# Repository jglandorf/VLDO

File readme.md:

## A Very Low Dropout Regulator Based on G4COL / ND6T

Implemented for use with the [QMX+ HF transceiver](https://qrp-labs.com/qmxp.html).  
PCB designed in KiCAD v9.

References:  
https://www.gqrp.com/limiter.jpg (
via https://groups.io/g/QRPLabs/topic/qmx_battery/111670594)  
http://www.nd6t.com/qrp/VLDO.htm

PCB, top  

PCB, bottom  

Schematic  

PCB layout  

LTSpice schematic for static simulation  

### Output Voltage with a 5V LDO 
The schematic uses a 5V LDO as the reference voltage.  The output voltage is given by: 
```  
Vldo = Vout * (R4 / (R3 + R4))
Vout = Vldo / (R4 / (R3 + R4))
12.5V = 5V / ( 20k / (30k + 20k))
11.8V = 5V / ( 22k / (30k + 22k))
8.85V = 5V / (39k / (30k + 39k))
```  
In practice, depending on the quality of transistors used, you may need to tweak the value of R3 or R4.

### Parts Tested in Prototype  
The PCB has alternate footprints for the active components so that alternative parts may be tested, or that the PCB may be built mostly surface-mount or through-hole.  

| RefDes | Part | Source | Comments           |   
| ------ | ----------- | -------------------- | ------------------------------------ |  
| M1 | IRF4905S | https://www.aliexpress.us/item/3256806571411100.html | (TO-263) Works, but runs hotter than expected; Rds_on likely much higher than spec
| M1 | IRF4905 | https://www.aliexpress.us/item/3256806880410046.html | (TO-220 alternate) Part from this supplier does not work well  
| U3 | ME6203A50M3G  | https://www.aliexpress.us/item/3256806655687105.html | (SOT23-3) Works well  
| Q3/Q4 | MMBT2222A  | https://www.aliexpress.us/item/3256806768261444.html | (SOT23-3) Works well  

### Power In/Out Connectors  
The prototype used Anderson PowerPole [PP15/30/45 housings](https://powerwerx.com/anderson-powerpole-colored-housings) with [PP45 crimp pins](https://powerwerx.com/anderson-261g2-powerpole-contact-pp45) as these were on hand -- not the [special PCB-mount pins](https://powerwerx.com/printed-circuit-board-pcb-contact-25amp).  
The PCB is designed for 14 AWG solid wire. To fit 14 AWG solid wire into a PP45 pin (which is designed for 10 AWG wire), it is folded over at the pin end, then soldered into the PP45 pin.  PP30 pins are deisgned for 12-14 AWG wire and should solder in directly.

14 AWG Wire folded over for PowerPole crimp pin  

14 AWG Wire soldered into PowerPole crimp pin  

14 AWG Wire soldered into PCB (be sure to cut excess lead length off)  

### Thermal Test  
Although the [QMX+](https://qrp-labs.com/qmxp.html) is specified to consume slightly less than 1 amp at 12 volts, the VLDO prototype was tested with a [WEL-3005 30W constant-current load tester](https://www.hackster.io/john-bradnam/30w-constant-current-load-65ecdd) at 2.5A.  
When using parts from AliExpress or of unknown pedigree, it is recommended that VLDO operating conditions do not exceed those normally expected for the QMX+; i.e., 1A@2 minutes (TX) / 0.1A@2 minutes (RX).   

Vin=13.24, Vout=12V (nominal)  
Iout=2.5A  
Q3/Q4=MMBT2222A  
U3=ME6203-5.0  
M1=IRF4905S (TO-263), __no heatsink__   

Temperature measured with a Cen-Tech 69465 infrared pyrometer aimed at M1's black marked surface, dist= 0.75", or at the bottom of the PCB directly under M1 at a distance of 0.75".  

| Time, seconds | T (deg C), M1 top | T (deg C) PCB bottom |
| ------------- | ----------------- | --------------- |  
| 0 | 22 | 20.6 |  
| 30 | 41.8 | 37.8 |  
| 60 | 52.8 | 47.4 |  
| 90 | 59.1 | 53.4 |  
| 120 | 62.5 | 56.8 |  
| 180 | 62.6 | 58.8 |  
| 240 | 64.4 | --- |  
| 300 | 65.4 | 60.3 |  
| 360 | 66.6 | 62.6 |  

### Rds(on) Measurement  
Rds(on) Measurement  
The IRF4905S's "ON" resistance, Rds(on), was measured with a 
[WEL-3005](https://www.hackster.io/john-bradnam/30w-constant-current-load-65ecdd) load tester 
and a UT161E multimeter.  For each constant-current test of Id below, current was only turned 
on for 3-4 seconds-- long enough to measure one parameter, but short enough to avoid significantly
heating the device. Power was supplied with a 9Ah LiFePo battery, nominal 12V output.

Device: IRF4905S from [this AliExpress vendor](https://www.aliexpress.us/item/3256806571411100.html).  
Rds(on) = Vds / Id  

| Vin, V |  Id, A | Vds, V | Vout, V | Rds(on)†, Ω |  
| --- | --- | --- | ---- | --- |  
| 13.33 | 0.00 | 1.13 | 12.16 | --- |  
| 13.28 | 0.50 | 1.12 | 12.13 | 2.24 |  
| 13.29 | 1.00 | 1.10 | 12.13 | 1.10 |  
| 13.20 | 1.50 | 1.06 | 12.12 | 0.71 |  
| 13.16 | 2.00 | 1.01 | 12.12 | 0.51 |  
| 13.11 | 2.50 | 0.96 | 12.11 | 0.38 |  

†Rds(on) is calculated; other table values are measured.

At 2 amps, the LTSpice [simulation](design/vldo_nd6t1.asc) reports an Rds(on) value of ~21.6mΩ.  The OEM's IRF4905S [datasheet](datasheets/MOSFET_P-Channel-irf4905s-datasheet-en_Infineon.pdf) says it should be ~20mΩ @Vgs = -10V, Id = -42A.

### Vdo (dropout voltage) Measurement
The IRF4905S's dropout voltage, was measured with a 
[WEL-3005](https://www.hackster.io/john-bradnam/30w-constant-current-load-65ecdd) load tester,
a [UT161E](https://meters.uni-trend.com/product/ut161-series/) multimeter, and a [Hanmatek HM305](http://www.hanmatek.cn/en/index.php?s=/Show/index/cid/14/id/12.html) adjustable power supply.
For each constant-current test of Id, below, current was only turned on for 3-4 seconds-- long enough to measure one parameter, but short enough to avoid significantly
heating the device.  

Dropout Voltage when Vin is close to the nomimal Vout:  
| Vin, V |  Id, A | Vout, V | ΔVout-Vin, V |  
| --- | --- | --- | ---- |  
| 12.10 | 0.00 | 12.11 | 0.01 |  
| 12.10 | 0.50 | 12.05 | -0.05 |  
| 12.10 | 1.00 | 12.00 | -0.10 |  
| 12.10 | 1.50 | 11.95 | -0.15 |  
| 12.10 | 2.00 | 11.90 | -0.20 |  
| 12.10 | 2.50 | 11.84 | -0.26 |  

For a nominal QMX+ TX current of somewhat under 1A, the dropout voltage is ~150mV using the IRF4905S from [this AliExpress vendor](https://www.aliexpress.us/item/3256806571411100.html).  Vdo should be lower using a higher quality part.

(Vout - Vin) Voltage at 1A:
  
Additional data is [here](tests/vldo_tests.ods).

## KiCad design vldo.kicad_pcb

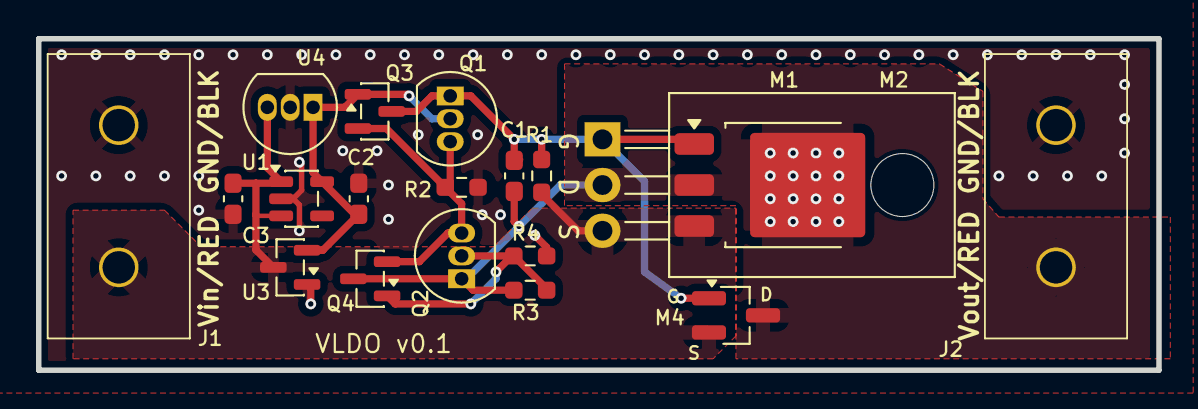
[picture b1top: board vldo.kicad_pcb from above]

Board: 2 copper layers, 62.2 x 18.4 mm, 19 parts (0 on the bottom side), 7 nets.

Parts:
C1: 1µ; C_0603_1608Metric_Pad1.08x0.95mm_HandSolder
C2: 0.1; C_0603_1608Metric_Pad1.08x0.95mm_HandSolder
C3: 0.1µ; C_0603_1608Metric_Pad1.08x0.95mm_HandSolder
J1, J2: PP15; Anderson_Powerpole-25A-V_Dual
M1: IRF4905; TO-252-3_TabPin2
M2: IRF4905; TO-220-3_Horizontal_TabDown
M4: SI2301; SOT-23_MOSFET_GSD_Handsoldering
Q1, Q2: 2N2222; TO-92_Inline
Q3, Q4: MMBT2222A; SOT-23
R1: 100k; R_0603_1608Metric_Pad0.98x0.95mm_HandSolder
R2: 10k; R_0603_1608Metric_Pad0.98x0.95mm_HandSolder
R3: 30k; R_0603_1608Metric_Pad0.98x0.95mm_HandSolder
R4: 22k; R_0603_1608Metric_Pad0.98x0.95mm_HandSolder
U1: TPS7A0508PDBV; SOT-23-5
U3: MCP1703Ax-500xxTT; SOT-23
U4: MC78L05_TO92; TO-92_Inline

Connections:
0: C2.2, C3.2, J1.2, J2.2, R2.2, R4.2, U1.2 (GND), U3.1 (GND), U4.2 (GND)
/M1G: C1.2, M1.1 (G), M2.1 (G), M4.1 (G), Q1.1 (C), Q3.3 (C), R1.2
/Q2B: Q2.2 (B), Q4.1 (B), R3.2, R4.1
/Q12E: Q1.3 (E), Q2.3 (E), Q3.2 (E), Q4.2 (E), R2.1
/Vout: C1.1, J2.1, M1.2 (D), M2.2 (D), M4.3 (D), Q2.1 (C), Q4.3 (C), R3.1
Vin: C3.1, J1.1, M1.3 (S), M2.3 (S), M4.2 (S), R1.1, U1.1 (IN), U1.3 (EN), U3.3 (VI), U4.3 (VI)
Vldo: C2.1, Q1.2 (B), Q3.1 (B), U1.5 (OUT), U3.2 (VO), U4.1 (VO)

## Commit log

2025-12-08 Initial commit for working prototypes
2025-12-08 Update readme.md.
2025-12-09 Update readme.md with 'Rds(on)' info.
2025-12-10 Add dropout voltage tests.

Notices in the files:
vldo.kicad_pcb:
Artwork (C) 2025, AC8ES
